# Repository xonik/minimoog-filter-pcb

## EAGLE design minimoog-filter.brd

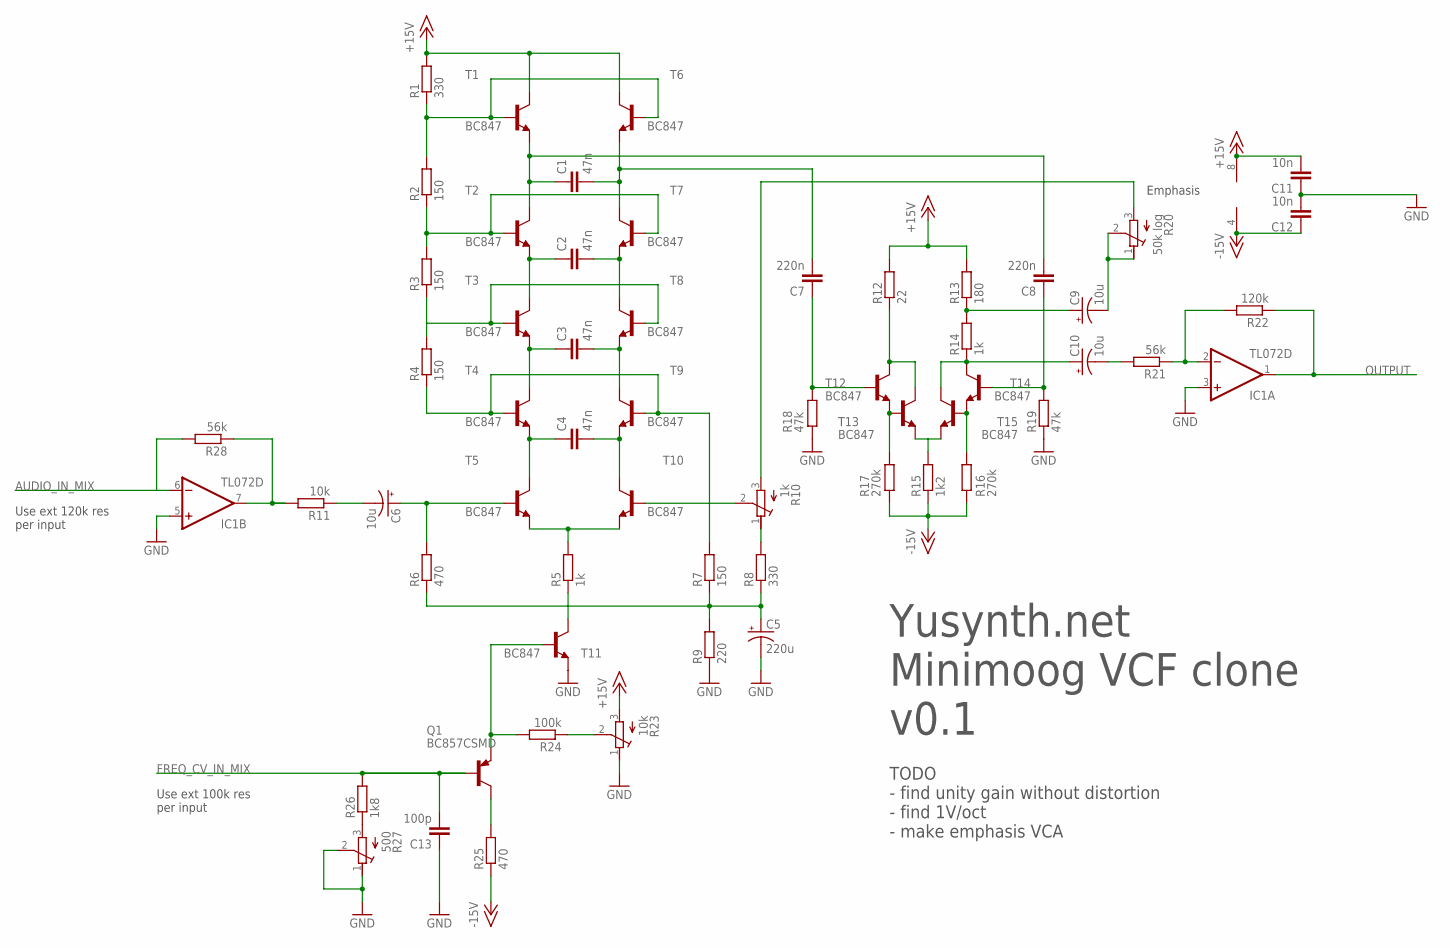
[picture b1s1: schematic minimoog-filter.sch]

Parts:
C1, C2, C3, C4: 47n; C0805
C5: 220u; E2-5
C6, C9, C10: 10u; E2-5
C7, C8: 220n; C0805
C11, C12: 10n; C0805
C13: 100p; C0805
IC1: TL072D; SO08
Q1: BC857CSMD; SOT23-BEC
R1, R8: 330; R0805
R2, R3, R4, R7: 150; R0805
R5, R14: 1k; R0805
R6, R25: 470; R0805
R9: 220; R0805
R10: 1k; RTRIMT93YA
R11: 10k; R0805
R12: 22; R0805
R13: 180; R0805
R15: 1k2; R0805
R16, R17: 270k; R0805
R18, R19: 47k; R0805
R20: 50k log; RTRIMT93YA
R21, R28: 56k; R0805
R22: 120k; R0805
R23: 10k; RTRIMT93YA
R24: 100k; R0805
R26: 1k8; R0805
R27: 500; RTRIMT93YA
T1, T2, T3, T4, T5, T6, T7, T8, T9, T10, T11, T12, T13, T14, T15: BC847; SOT23

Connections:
+15V: C11.2, IC1.8 (V+), R1.2, R12.2, R13.2, R23.3 (E), T1.3 (C), T6.3 (C)
-15V: C12.1, IC1.4 (V-), R15.1, R16.1, R17.1, R25.1
AUDIO_IN_MIX: IC1.6 (-IN), R28.2
FREQ_CV_IN_MIX: C13.2, Q1.B, R26.2
GND: C5.-, C11.1, C12.2, C13.1, IC1.3 (+IN), IC1.5 (+IN), R9.1, R18.1, R19.1, R23.1 (A), R27.1 (A), R27.2 (S), T11.2 (E)
unnamed: C1.1, C8.2, T1.2 (E), T2.3 (C)
unnamed: C1.2, C7.2, T6.2 (E), T7.3 (C)
unnamed: C2.1, T2.2 (E), T3.3 (C)
unnamed: C2.2, T7.2 (E), T8.3 (C)
unnamed: C3.1, T3.2 (E), T4.3 (C)
unnamed: C3.2, T8.2 (E), T9.3 (C)
unnamed: C4.1, T4.2 (E), T5.3 (C)
unnamed: C4.2, T9.2 (E), T10.3 (C)
unnamed: R5.2, T5.2 (E), T10.2 (E)
unnamed: R2.1, R3.2, T2.1 (B), T7.1 (B)
unnamed: R1.1, R2.2, T1.1 (B), T6.1 (B)
unnamed: R3.1, R4.2, T3.1 (B), T8.1 (B)
unnamed: R4.1, R7.2, T4.1 (B), T9.1 (B)
unnamed: R10.2 (S), T10.1 (B)
unnamed: C7.1, R18.2, T12.1 (B)
unnamed: R5.1, T11.3 (C)
unnamed: C5.+, R6.1, R7.1, R8.1, R9.2
unnamed: C9.+, R13.1, R14.2
unnamed: R8.2, R10.1 (A)
unnamed: C6.+, R6.2, T5.1 (B)
unnamed: C6.-, R11.1
unnamed: C10.+, R14.1, T14.3 (C), T15.3 (C)
unnamed: R16.2, T14.2 (E), T15.1 (B)
unnamed: R17.2, T12.2 (E), T13.1 (B)
unnamed: R12.1, T12.3 (C), T13.3 (C)
unnamed: R15.2, T13.2 (E), T15.2 (E)
unnamed: C8.1, R19.2, T14.1 (B)
unnamed: R10.3 (E), R20.3 (E)
unnamed: C9.-, R20.1 (A), R20.2 (S)
unnamed: C10.-, R21.2
unnamed: IC1.2 (-IN), R21.1, R22.2
unnamed: R23.2 (S), R24.1
unnamed: Q1.E, R24.2, T11.1 (B)
unnamed: Q1.C, R25.2
unnamed: R26.1, R27.3 (E)
unnamed: IC1.7 (OUT), R11.2, R28.1
OUTPUT: IC1.1 (OUT), R22.1

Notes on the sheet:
Emphasis
Use ext 100k res per input
Use ext 120k res per input
Yusynth.net Minimoog VCF clone v0.1
TODO - find unity gain without distortion - find 1V/oct - make emphasis VCA

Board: 2 copper layers, 58 parts (0 on the bottom side), 42 nets, no tracks yet.

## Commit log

2018-07-20 First commit, drawn yusynth.net circuit, yet to make emphasis vca and test responses
2020-02-26 Added git ignore
2022-04-08 moving
